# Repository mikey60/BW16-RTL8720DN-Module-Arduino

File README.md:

### **BW16 (RTL8720DN) Module - Getting Started with Arduino**
**Revisions**

- **March 3, 2021** - Implemented the recommendation from @moononournation that changes the variant.cpp file to be compatible with the SPI1 pin definition in the SPI.cpp file. This simplifies the sketches that use SPI so that the creation of another SPIClass is not required. So this is a 'major' change for the sketches that use SPI.  A new 'modified variant.cpp can be found in the variant_cpp_mod folder.  I also corrected and updated some comments in the sketches.

- **March 17, 2021** - Slightly updated the RTL8720DN multi function board with additional Power and ground connection holes.  Added a sketch for rtlduino/BW16 board.  The sketch describes the modifications to make the board more useful.

- **March 24, 2021** - Added RTL8720DN/BW16 and rtlduino pinout images supplied by @moononournation.

- **March 28, 2021** - Small corrections, add information on rtlduino modifications and link to @moononournation Instructable to program rtlduino.

- **July 7, 2021** - Include a modified variant.h file in the variant_cpp_mod folder so the AT serial can be used as noted by @flowlow in the issues.

**Background**

- I decided to try the BW16 (RTL8720DN) module because it supports 5GHz WiFi and my 2.4 GHz WiFi band is very busy with old electronics, WiFi security cameras, neighbors networks, microwave oven and many IOT 2.4 GHz only (ESP8266 and ESP32) modules connected. My 2.4 GHz channel can quite often spike over to over 40% utilization whereas my 5GHz channel is less than 10%. I also recommend creating a second WLAN with only a 5 GHz channel.  It should also use a different SSID than the main WLAN.  That way the module can only connect to the 5 GHZ and won't connect to the 2.4 GHz because it has a stronger signal.

- The module I purchased is from Digikey for $4.25 Part number ‎1597-102110419-ND‎, manufactured by Seeed Technology Co., Ltd.  It can be purchased on ebay, AliExpress, and of course the Seed Studio website.

**Getting Started with Arduino and BW16 Module**

- To get started with arduino I used the ambd_arduino package found at https://github.com/ambiot/ambd_arduino/tree/master/Arduino_package.  
- I followed the Arduino IDE installation instructions as outlined in step 2 of the webpage at https://www.amebaiot.com/en/amebad-arduino-getting-started/
- One the package is installed the variant.cpp file needs to be modified to map some of the pins of the BW16 module.  This file can be found at **"C:\Users\your_user\AppData\Local\Arduino15\packages\realtek\hardware\AmebaD\3.0.7\variants\rtl8721d\variant.cpp"**  where "your_user" is the user name of the your windows login.  Version 3.0.7 was the latest version at this time. The modified file can be found in the variant_cpp_mod folder. The modifications made to the variant.cpp file are shown in the 'variant.cpp changes.png file found in the info folder.   The original variant.cpp file will have to be replaced with the modified file every time the package is updated.  I am sure that there is a better way to do this probably by creating a RTL8720DN/BW16 variant. Thanks to @moononournation, pinout pictures for the RTL8720DN and the rtlduino devices that include the Arduino pin numbers defined in the modified variant.cpp file are shown below. Larger images of the pinouts can be found in the Info folder.

<IMG SRC="https://github.com/mikey60/BW16-RTL8720DN-Module-Arduino/blob/main/Info/RTL8720DN_Pinout_Small.png">

<IMG SRC="https://github.com/mikey60/BW16-RTL8720DN-Module-Arduino/blob/main/Info/rtlduino_Pinout_Small.png">

- Many of the example sketches of the repository found in the sketches folder have been modified from the original examples in the Realtek Arduino package. In many cases the pin numbers were changed to work with the BW16 module.  I also modified code to use the hardware SPI channel 1 of the BW16 module.
- I could not figure out how to easily get the BW16 module to work with the FastLED library so I opted to use the APA102/sk9822 LED strips that use both data and clock lines and can be driven with the SPI hardware.
- The Hard way to get started is to attach breadboard interconnect pigtails to all the pins of the BW16 module.  See the Hard_way_to_test pictures in the info folder.
- An easy way to get started is to solder the module to an ESP8266 Serial Wireless WiFi Module Adapter Plate.  These are ones I purchased: <https://www.amazon.com/gp/product/B07WDBLQ7H/ref=ppx_yo_dt_b_asin_title_o02_s00?ie=UTF8&psc=1> The pulldown resistor on pin 10 should be removed.  I did not install the LDO regulator.  I just plugged the module adapter into a solder-less breadboard and supplied +3.3 volts to the VCC pin and ground to the GND pin.  I connected a SPST switch from pin 3 (CHIP_EN) to ground and a second SPST switch from pin 11 (PA7) to ground through a 2K resistor to put the module in download mode like the ESP modules. I then used a USB to 3.3v TTL adapter to connect to TXD (PA7) and RXD (PA8) pins. See the pdf schematic in the 'RTL8720DN multi function board' folder for reference for the connections.   A BW16 product specification can be found in the info folder. A picture of the board with the mounted BW16 module and the labeled pins is shown below.

<IMG SRC="https://github.com/mikey60/BW16-RTL8720DN-Module-Arduino/blob/main/Info/BW16%20on%20ESP-07%20Breakout%20Board.jpg">

- Before downloading you can interact with the BW16 module using pins 15 (PB2/LP_UART_RXD) and pin 16 (PB1/LP_UART_TXD) connected to the USB to 3.3v TTL adapter with AT commands. You can also interact with the Test Command Mode by connecting the USB to 3.3v TTL adapter to the TXD (PA7) and RXD (PA8) pins.  See the txt files in the info folder for brief captures of the interactions.  Note that once the BW16 module is downloaded with an arduino sketch those interfaces are no longer available unless you somehow reload the original firmware.
- **To put the module in the download mode:**

        Press and hold the switch to PA7.
        Press and release the switch to the CHIP_EN pin.
        Release the switch to PA7.  
- A another way to use the BW16 module is to use an ESP8266 Burning Fixture Development Board but that requires some cuts, jumpers and a resistor to work properly.  Then a separate 3.3 volt power supply and USB to 3.3v TTL adapter are not required.
- The 'RTL8720DN multi function board' folder contains all the files for a 'general purpose' PCB that I created using KiCad for the door switch and MQTT Digital LED projects.
- rtlduino module modifications - In my opinion the USB port should be connected to the LOG_TX and LOG_RX pins rather than the AT_TX and AT_RX pins. I don’t believe that many people use the AT port. The first thing I did is cut and jumper the board so the USB port was connected to the LOG port so I could do downloads and terminal interaction with the USB using Arduino. Also I replaced the zero ohm resistor in series with the burn switch with 1.8 Kohm to comply with the >1 Kohm of the ‘GPIO Pull Low Restriction’ of the RTL872xD data sheet. See the 'rtlduino_modifications.pdf' file in the Info folder.  Another way to program the rtlduino can be found at https://www.instructables.com/RTL8720DN/.

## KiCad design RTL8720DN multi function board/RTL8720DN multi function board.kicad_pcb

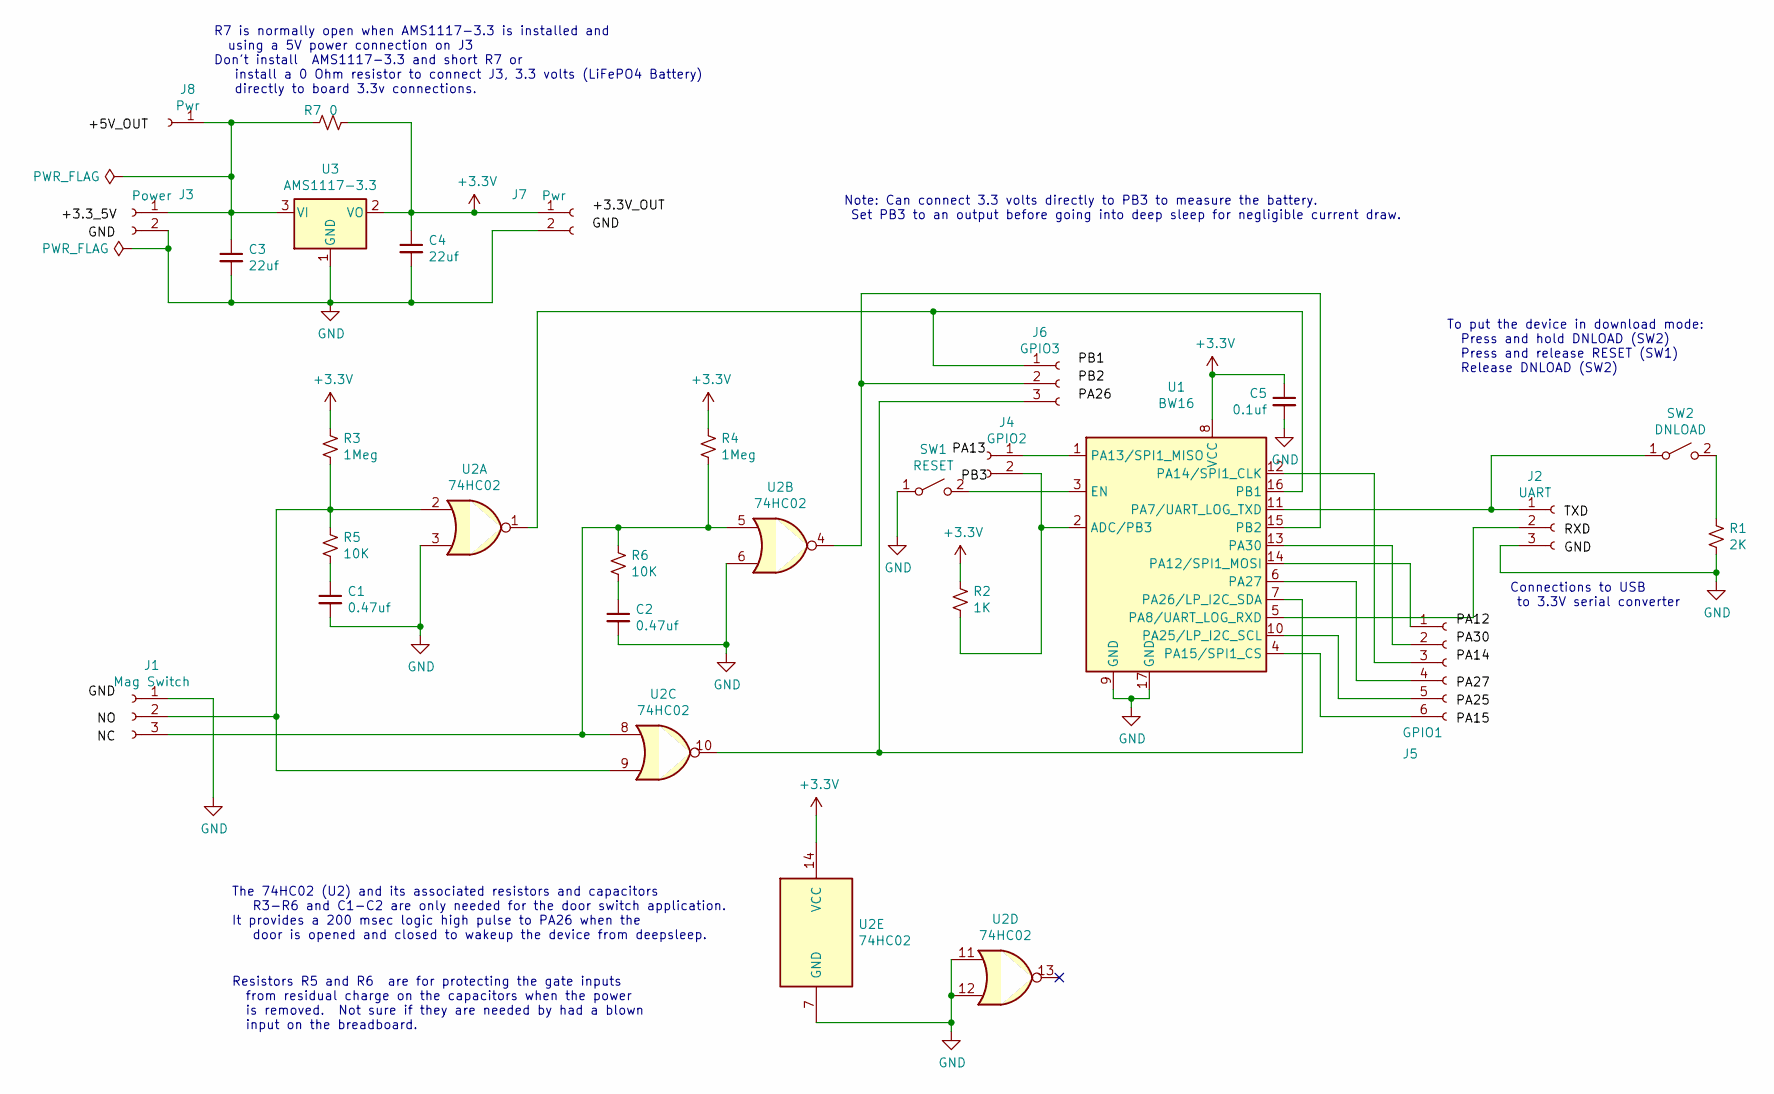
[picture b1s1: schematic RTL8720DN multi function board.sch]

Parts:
C1, C2: 0.47uf; R_0805_2012Metric_Pad1.15x1.40mm_HandSolder
C3, C4: 22uf; R_1210_3225Metric_Pad1.42x2.65mm_HandSolder
C5: 0.1uf; R_0805_2012Metric_Pad1.15x1.40mm_HandSolder
J1: Mag Switch; PinHeader_1x03_P2.54mm_Vertical
J2: UART; PinHeader_1x03_P2.54mm_Vertical
J3: Power; PinHeader_1x02_P2.54mm_Vertical
J4: GPIO2; PinHeader_1x02_P2.54mm_Vertical
J5: GPIO1; PinHeader_1x06_P2.54mm_Vertical
J6: GPIO3; PinHeader_1x03_P2.54mm_Vertical
J7: Pwr; PinHeader_1x02_P2.54mm_Vertical
J8: Pwr; PinHeader_1x01_P2.54mm_Vertical
R1: 2K; R_0805_2012Metric_Pad1.15x1.40mm_HandSolder
R2: 1K; R_0805_2012Metric_Pad1.15x1.40mm_HandSolder
R3, R4: 1Meg; R_0805_2012Metric_Pad1.15x1.40mm_HandSolder
R5, R6: 10K; R_0805_2012Metric_Pad1.15x1.40mm_HandSolder
R7: 0; R_0805_2012Metric_Pad1.15x1.40mm_HandSolder
SW1: RESET; SW_SPST_EVQPE1
SW2: DNLOAD; SW_Push_SPST_NO_Alps_SKRK
U1: BW16
U2: 74HC02; SOIC-14_3.9x8.7mm_P1.27mm
U3: AMS1117-3.3; SOT-223-3_TabPin2

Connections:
+3V3: C4.1, C5.1, J7.1, R2.1, R3.1, R4.1, R7.1, U1.8 (VCC), U2.14 (VCC), U3.2 (VO)
GND: C1.2, C2.2, C3.2, C4.2, C5.2, J1.1, J2.3, J3.2, J7.2, R1.1, SW1.1 (A), U1.9 (GND), U1.17 (GND), U2.3, U2.6, U2.7 (GND), U2.11, U2.12, U3.1 (GND)
unnamed: C1.1, R5.1
unnamed: C2.1, R6.1
unnamed: C3.1, J3.1, J8.1, R7.2, U3.3 (VI)
unnamed: J1.2, R3.2, R5.2, U2.2, U2.9
unnamed: J1.3, R4.2, R6.2, U2.5, U2.8
unnamed: J2.1, SW2.1 (A), U1.11 (PA7/UART_LOG_TXD)
unnamed: J2.2, U1.5 (PA8/UART_LOG_RXD)
unnamed: J4.1, U1.1 (PA13/SPI1_MISO)
unnamed: J4.2, R2.2, U1.2 (ADC/PB3)
unnamed: J5.1, U1.14 (PA12/SPI1_MOSI)
unnamed: J5.2, U1.13 (PA30)
unnamed: J5.3, U1.12 (PA14/SPI1_CLK)
unnamed: J5.4, U1.6 (PA27)
unnamed: J5.5, U1.10 (PA25/LP_I2C_SCL)
unnamed: J5.6, U1.4 (PA15/SPI1_CS)
unnamed: J6.1, U1.16 (PB1), U2.1
unnamed: J6.2, U1.15 (PB2), U2.4
unnamed: J6.3, U1.7 (PA26/LP_I2C_SDA), U2.10
unnamed: R1.2, SW2.2 (B)
unnamed: SW1.2 (B), U1.3 (EN)

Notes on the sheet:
Connections to USB to 3.3V serial converter
To put the device in download mode: Press and hold DNLOAD (SW2) Press and release RESET (SW1) Release DNLOAD (SW2)
R7 is normally open when AMS1117-3.3 is installed and using a 5V power connection on J3 Don't install AMS1117-3.3 and short R7 or install a 0 Ohm resistor to connect J3, 3.3 volts (LiFePO4 Battery) directly to board 3.3v connections.
The 74HC02 (U2) and its associated resistors and capacitors R3-R6 and C1-C2 are only needed for the door switch application. It provides a 200 msec logic high pulse to PA26 when the door is opened and closed to wakeup the device from deepsleep.
Resistors R5 and R6 are for protecting the gate inputs from residual charge on the capacitors when the power is removed. Not sure if they are needed by had a blown input on the breadboard.
Note: Can connect 3.3 volts directly to PB3 to measure the battery. Set PB3 to an output before going into deep sleep for negligible current draw.

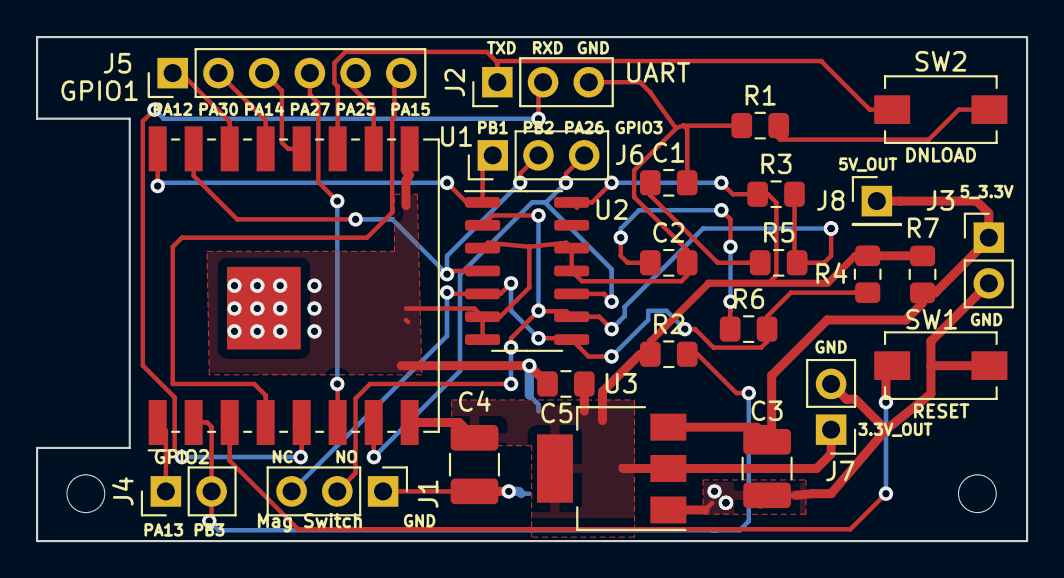
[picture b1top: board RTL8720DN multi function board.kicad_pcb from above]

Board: 2 copper layers, 55.0 x 28.0 mm, 27 parts (0 on the bottom side), 22 nets.

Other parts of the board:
Hole1, Hole2: 2.1mm; MountingHole_2.1mm

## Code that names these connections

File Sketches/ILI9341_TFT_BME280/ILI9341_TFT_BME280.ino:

/*
 * This sketch demonstrates how to use TFT LCD with ILI9314 api to display BME20 sensor
 * data 
 * Pre-requirement:
 *     an ILI9341 TFT LCD with SPI interface; Note VCC = 3.3V and LED = 5V
 *     BME20 sensor connected to I2C interface
 *     BW16 Module/ RTL8720 Pins: SDA = 17(PA26), SCL = 16(PA25)
 * Updated 3/2/2021 to use SPI1 without creating a seperate SPIClass
 * SPI1 Pins: MOSI = 21(PA12), MISO = 20(PA13), Clk = 19(PA14), CS = 18(PA15)
 
***************************************************************************

  This is a library for the BME280 humidity, temperature & pressure sensor

  Designed specifically to work with the Adafruit BME280 Breakout
  ----> http://www.adafruit.com/products/2650

  These sensors use I2C or SPI to communicate, 2 or 4 pins are required
  to interface. The device's I2C address is either 0x76 or 0x77.

  Adafruit invests time and resources providing this open source code,
  please support Adafruit andopen-source hardware by purchasing products
  from Adafruit!

  Written by Limor Fried & Kevin Townsend for Adafruit Industries.
  BSD license, all text above must be included in any redistribution
 ***************************************************************************/
 // I2C Interface: Default for BW16 (RTL8720DN) : SCL=PA25, SDA=PA26



#include <Wire.h>
#include <Adafruit_Sensor.h>
#include <Adafruit_BME280.h>

#include <SPI.h>
/*  myspiILI9341.cpp is modified from original AmebaILI9341.cpp file in SPI library for 
    BW16(RTL8720DN) module */
#include "myspiILI9341.h"

#if defined(BOARD_RTL8195A)
#define TFT_RESET       8
#define TFT_DC          9
#define TFT_CS          10
#elif defined(BOARD_RTL8710)
#define TFT_RESET       5
#define TFT_DC          2
#define TFT_CS          10
#elif defined(BOARD_RTL8721D) // Works for RTL8720DN (BW16 module) with re-defined pins in variant.cpp
#define TFT_RESET       1   //PB1
#define TFT_DC          2   //PB3
#define TFT_CS          18  //PA15
//#define TFT_CLK         19  //PA14
//#define TFT_MOSI        20  //PA12
//#define TFT_MISO        21  //PA13
#endif

// For SPI interface only
#define BME_SCK 13
#define BME_MISO 12
#define BME_MOSI 11
#define BME_CS 10

#define SEALEVELPRESSURE_HPA (1013.25)
Adafruit_BME280 bme; // I2C used for this example
//Adafruit_BME280 bme(BME_CS); // hardware SPI
//Adafruit_BME280 bme(BME_CS, BME_MOSI, BME_MISO, BME_SCK); // software SPI




myspiILI9341 tft = myspiILI9341(TFT_CS, TFT_DC, TFT_RESET);

void setup() {
    Serial.begin(115200);
    Serial.println("BME280 Sensor Data displayed on ILI9341 TFT display"); 
    Wire.begin();  // I2C Interface: Default for BW16 (RTL8720DN) : SCL=PA25, SDA=PA26  
    bool status;    
    // default settings
    status = bme.begin(0x76);
    if (!status) {
        Serial.println("Could not find a valid BME280 sensor, check wiring!");
        while (1);
    }

    tft.begin();
    tft.setRotation(3);
}

void loop() { 
    displayValues();
    delay(5000);
}


void displayValues() {
    tft.clr();
    tft.setCursor(3, 3);

    tft.setForeground(ILI9341_WHITE);
    tft.setFontSize(4);
    tft.println("BME280 Sensor");
    tft.println();
    tft.setFontSize(2);
     
    tft.setForeground(ILI9341_RED);
    tft.print(" Temperature = ");
    tft.print(bme.readTemperature());
    tft.println(" deg C");
    tft.println();
    
    tft.setForeground(ILI9341_GREEN);
    tft.print(" Pressure = ");
    tft.print(bme.readPressure() / 100.0F);
    tft.println(" hPa");
    tft.println();
    
    tft.print(" Altitude ~= ");
    tft.print(bme.readAltitude(SEALEVELPRESSURE_HPA));
    tft.println(" m");
    tft.println();

    tft.setForeground(ILI9341_BLUE);
    tft.print(" Humidity = ");
    tft.print(bme.readHumidity());
    tft.println(" %");

    tft.drawRectangle(0,0,340,200,ILI9341_ORANGE);

}

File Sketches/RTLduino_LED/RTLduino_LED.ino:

/* Program to drive the RGB LED on the rtlduino version 1.0 board with the BW16 module.
 * Note: I cut the AT_TX(PB1) and AT_RX(PB2) connections from the BW16 module at the 
 * pins 3 and 2 of CH340 chip and jumpered the CH340 pins 3 and 2 to LOG_TX(PA7) and 
 * LOG_RX(PA8) to be able to download the device.  I also changed the 0 ohm resistor in 
 * series with the burn switch to meet the RTL872X requirements for the minimum 
 * resistance to ground. This resistor is connected to LOG_TX to enable download mode.
 */
const int LED_red = 21;    //PA12 based on edit of variant.cpp
const int LED_green = 19;  //PA14 based on edit of variant.cpp
const int LED_blue = 20;   //PA13 based on edit of variant.cpp

void setup(){
    Serial.begin(115200);
    pinMode(LED_red, OUTPUT);
    pinMode(LED_green, OUTPUT);
    pinMode(LED_blue, OUTPUT);
    digitalWrite(LED_red, LOW);
    digitalWrite(LED_green, LOW);
    digitalWrite(LED_blue, LOW);
}

void loop() {

    digitalWrite(LED_red, HIGH);
    Serial.println("Red LED");
    delay(3000);
    digitalWrite(LED_red, LOW);
    digitalWrite(LED_green, HIGH);
    Serial.println("Green LED");
    delay(3000);
    digitalWrite(LED_green, LOW);
    digitalWrite(LED_blue, HIGH);
    Serial.println("Blue LED");
    delay(3000);
    digitalWrite(LED_blue, LOW);
}

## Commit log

2021-02-17 update info
2021-02-17 update info and README
2021-02-17 README
2021-02-17 update jpegs
2021-02-24 update comments
2021-03-04 Update per @moononournation SPI1 suggestion
2021-03-17 pcb and rtlduino update
2021-03-24 Documentation Corrections
2021-03-24 Add pinout diagrams
2021-03-28 rtlduino updates
2021-07-07 Include modified variant.h for AT serial
